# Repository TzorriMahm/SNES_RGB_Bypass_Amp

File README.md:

# SNES RGB Bypass Amp
**A modding board to bypass the SNES' video encoder by using TI's THS7374 video amplifier, to achieve optimised RGB video.**<br>

This modification works with all 1-Chip models (PAL/NTSC).

<br><br>
**⁓ Designed with ♥ in Germany ⁓**<br><br>

# Where to get the PCB?
You can order the PCB directly from [OSHPark](https://oshpark.com/shared_projects/o16zk0W4).
Of course, feel free to use the gerber files with any manufacturer of your choice.<br>
Use 0.8mm board thickness to ensure an easy and clean installation.

# Before you start
Make sure that your console is a 1-Chip model. If your console is a SNES2/Mini/Jr., this is the case by default.<br>
Otherwise, this can easily done by looking for an indicator at the main board:

# Install instructions
## PAL consoles (SNSP-001)
### Preparing the SNES main board
**1-CHIP-01/02 models**
- disconnect +12V from MultiOut Pin 3: **remove R28**
- disconnect stock RGB: **remove R15, R16, R17**
- remove decoupling caps from MultiOut (optional**¹**): **remove C44, C45, C46, C47**

### Installing the modding board
- isolate the bottom side of the modding board to avoid any shorts
- solder the modding board onto the pins of the MultiOut
- solder a wire from the via next to R6 (SNES main board) to pad 'R' (modding board)
- solder a wire from the via next to R7 (SNES main board) to pad 'G' (modding board)
- solder a wire from the via next to R8 (SNES main board) to pad 'B' (modding board)  
- solder a wire from the via that is nearest the bottom left corner of designator C6 (SNES main board) to pad 'CS' (modding board)  

### Install diagram (PAL 1-CHIP)

## NTSC consoles (SNS-001/SHVC-001)
### Preparing the SNES main board
**1-CHIP-01/02 models**<br>
These models already have C-Sync connected to pin 3 of the MultiOut.<br>
You can either use this (not recommended) or:
- disconnect C-Sync from MultiOut Pin 3: **remove R12** (optionally **remove R9, R10, R11, Q1** as well)
- disconnect stock RGB: **remove R15, R16, R17**
- remove decoupling caps from MultiOut (optional**¹**): **remove C44, C45, C46, C47**

**1-CHIP-03 model**<br>
This model hasn't C-Sync connected at all, so you'll have nothing to do here.
- disconnect stock RGB:	**remove R15, R16, R17**
- remove decoupling caps from MultiOut (optional**¹**'**²**):	**remove C44, C45, C47**

### Installing the modding board
- isolate the bottom side of the modding board to avoid any shorts
- solder the modding board onto the pins of the MultiOut
- solder a wire from the via next to R6 (SNES main board) to pad 'R' (modding board)
- solder a wire from the via next to R7 (SNES main board) to pad 'G' (modding board)
- solder a wire from the via next to R8 (SNES main board) to pad 'B' (modding board) 
- solder a wire from the via under the left pad of R9 (SNES main board) to pad 'CS' (modding board)

### Install diagram (NTSC 1-CHIP)

## NTSC model 2 / SNES2/Mini/Jr. (SNS-101/SHVC-101)
### Preparing the SNES main board
**SNN-CPU-01 model**<br>
Since this model doesn't have stock RGB, here is no preparation needed.

### Installing the modding board
- isolate the bottom side of the modding board to avoid any shorts
- solder the modding board onto the pins of the MultiOut
- solder wires from the vias (shown in the install diagram below) to the appropriate pads on the modding board

### Install diagram (SNES2/Mini/Jr.)

### Notes
**¹** if you remove the decoupling caps at the MultiOut, make sure to occupy C22, C32, C42 & C51 on the modding board! Never use both at the same time!<br>
**²** if you leave the decoupling caps at the MultiOut, make sure to occupy **at least** C51 on the modding board! (1-CHIP-03 only!) 

# Troubleshooting
Double-check continuity between connections:
- 'R' (modding board) ⇄ S-CPUN pin 156 / S-RGB pin 5 (SNES main board)
- 'G' (modding board) ⇄ S-CPUN pin 157 / S-RGB pin 3 (SNES main board)
- 'B' (modding board) ⇄ S-CPUN pin 158 / S-RGB pin 1 (SNES main board)
- 'CS' (modding board) ⇄ S-CPUN pin 151 / S-RGB pin 7 (SNES main board)

# Miscellaneous
#### Jumper 'J:LPF'
The THS7374 has a low pass filter on each of the four channels which can be turned on by shorting jumper 'J:LPF' on the modding board. This is mostly needed if you wire the console directly to a flat-screen TV. There's no need for the low pass filter on analogue devices.<br>
If you use an OSSC or a Framemeister, it's better to use their filter options.

#### Ghosting fix
In order to get rid of the ghosting issue (which 1-Chip models are known for), simply replace C11 (SNES main board) by a 470nF ceramic capacitor (0805 for normal/fat models, 0603 for SNES2/Mini/Jr.).

#### RGB cable
You will need a RGB cable with 220µF electrolytic capacitors on each of the 'R', 'G' & 'B' lines. The positive end is facing towards the console.<br>
This modding board is designed to output TTL level C-Sync directly at the MultiOut of the console.<br>
With that in mind, make sure you're using a suitable cable with a 470Ω resistor on the sync line to use it with most consumer products (like TV's, OSSC, Framemeister)!

# Disclaimer
I am not responsible for any damage to you, your devices or anything else!<br>
If you do the modification, you do it at your own risk and responsibility!

# Acknowledgement
Most of the credits should go to [borti4938](https://github.com/borti4938). He has made the actual (slightly different) circuit and inspired me to design this board. Thanks man! Thanks to Voultar for research and findig the ghosting fix! Thanks Bob, for your awesome and informative website [RetroRGB](http://retrorgb.com)!<br>
And of course, thanks to the whole retro gaming community for keeping the spirit alive!

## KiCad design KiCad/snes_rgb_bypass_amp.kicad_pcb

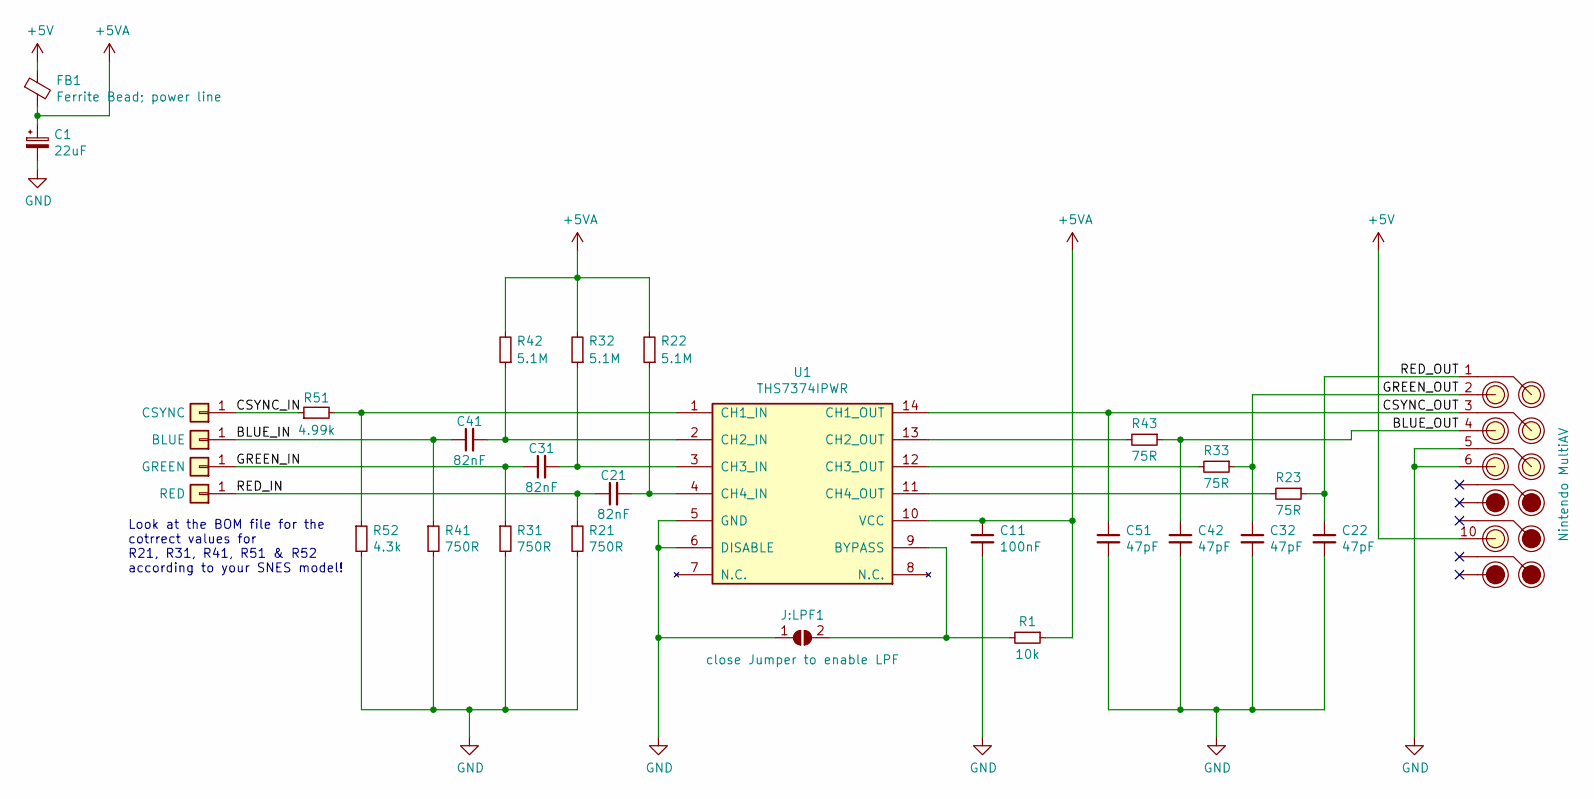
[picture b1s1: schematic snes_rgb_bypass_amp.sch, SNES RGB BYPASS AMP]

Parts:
C1: 22uF; C_SMD0805
C11: 100nF; C_SMD0603
C21, C31, C41: 82nF; C_SMD0603
C22, C32, C42, C51: 47pF; C_SMD0603
FB1: Ferrite Bead; power line; FB_SMD0603
INPUT_1: RED; SolderPad_customizable
INPUT_2: GREEN; SolderPad_customizable
INPUT_3: BLUE; SolderPad_customizable
INPUT_4: CSYNC; SolderPad_customizable
J:LPF1: close Jumper to enable LPF; SolderJumper_2x0.5x0.75mm
MultiAV1: Nintendo MultiAV; NintendoMultiAV_FB-gap
R1: 10k; R_SMD0603
R21, R31, R41: 750R; R_SMD0603
R22, R32, R42: 5.1M; R_SMD0603
R23, R33, R43: 75R; R_SMD0603
R51: 4.99k; R_SMD0603
R52: 4.3k; R_SMD0603
U1: THS7374IPWR; TSSOP-14

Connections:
+5V: FB1.1, MultiAV1.10
+5VA: C1.1, C11.1, FB1.2, R1.1, R22.2, R32.2, R42.2, U1.10 (VCC)
/BLUE_IN: C41.1, INPUT_3.1, R41.1
/BLUE_OUT: C42.1, MultiAV1.4, R43.1
/CSYNC_IN: INPUT_4.1, R51.1
/CSYNC_OUT: C51.1, MultiAV1.3, U1.14 (CH1_OUT)
/GREEN_IN: C31.1, INPUT_2.1, R31.1
/GREEN_OUT: C32.1, MultiAV1.2, R33.1
/RED_IN: C21.1, INPUT_1.1, R21.1
/RED_OUT: C22.1, MultiAV1.1, R23.1
GND: C1.2, C11.2, C22.2, C32.2, C42.2, C51.2, J:LPF1.1 (A), MultiAV1.5, MultiAV1.6, R21.2, R31.2, R41.2, R52.2, U1.5 (GND), U1.6 (DISABLE)
unnamed: C21.2, R22.1, U1.4 (CH4_IN)
unnamed: C31.2, R32.1, U1.3 (CH3_IN)
unnamed: C41.2, R42.1, U1.2 (CH2_IN)
unnamed: J:LPF1.2 (B), R1.2, U1.9 (BYPASS)
unnamed: R23.2, U1.11 (CH4_OUT)
unnamed: R33.2, U1.12 (CH3_OUT)
unnamed: R43.2, U1.13 (CH2_OUT)
unnamed: R51.2, R52.1, U1.1 (CH1_IN)

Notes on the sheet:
Look at the BOM file for the cotrrect values for R21, R31, R41, R51 & R52 according to your SNES model!

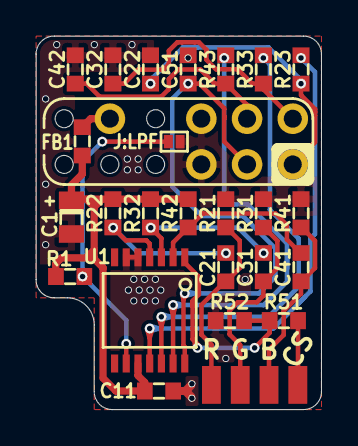
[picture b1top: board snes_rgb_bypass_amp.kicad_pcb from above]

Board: 2 copper layers, 15.9 x 20.8 mm, 30 parts (1 on the bottom side), 19 nets.

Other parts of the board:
***: TM_logo-silk

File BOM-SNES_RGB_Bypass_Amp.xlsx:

SNES RGB Bypass Amp - Bill of Materials
for normal/fat models
Designator | Mfr. No | Quantity | Description | Package | Value | Mouser
U1 | THS7374IPWR | 1 | 4-Ch. SD Video Amp | TSSOP-14 |  | https://www.mouser.de/ProductDetail/Texas-Instruments/THS737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
C1 | 08053D226MAT2A | 1 | Ceramic capacitor; X5R; 25V | SMD0805 | 22µF / 20% | https://www.mouser.de/ProductDetail/AVX/08053D226MAT2A?qs=bx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
C11 | 06035C104KAT2A | 1 | Ceramic capacitor; X7R; 50V | SMD0603 | 100nF / 10% | https://www.mouser.de/ProductDetail/AVX/06035C104KAT2A?qs=wO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
C21, C31, C31 | 0603YC823KAT2A | 3 | Ceramic capacitor; X7R; 16V | SMD0603 | 82nF / 10% | https://www.mouser.de/ProductDetail/AVX/0603YC823KAT2A?qs=Gc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
C22, C32, C42, C51 | 0603YC470KAT2A | 4 | Ceramic capacitor; X7R, 16V | SMD0603 | 47pF / 10% | https://www.mouser.de/ProductDetail/AVX/0603YC470KAT2A?qs=EU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
FB1 | MPZ1608S221ATA00 | 1 | Ferrite bead; power line | SMD0603 |  | https://www.mouser.de/ProductDetail/TDK/MPZ1608S221ATA00?qs=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
R1 | RC0603FR-0710KL | 1 | Resistor; 1/10W | SMD0603 | 10kΩ / 1% | https://www.mouser.de/ProductDetail/Yageo/RC0603FR-0710KL?qs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
R21, R31, R41 | RC0603FR-07750RL | 3 | Resistor; 1/10W | SMD0603 | 750Ω / 1% | https://www.mouser.de/ProductDetail/Yageo/RC0603FR-07750RL?q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
R22, R32, R42 | RC0603FR-075M1L | 3 | Resistor; 1/10W | SMD0603 | 5.1MΩ / 1% | https://www.mouser.de/ProductDetail/Yageo/RC0603FR-075M1L?qs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
R23, R33, R43 | RC0603FR-0775RL | 3 | Resistor; 1/10W | SMD0603 | 75Ω / 1% | https://www.mouser.de/ProductDetail/Yageo/RC0603FR-0775RL?qs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
R51 | RC0603FR-074K99L | 1 | Resistor; 1/10W | SMD0603 | 4.99kΩ / 1% | https://www.mouser.de/ProductDetail/Yageo/RC0603FR-074K99L?q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
R52 | RC0603FR-074K3L | 1 | Resistor; 1/10W | SMD0603 | 4.3kΩ / 1% | https://www.mouser.de/ProductDetail/Yageo/RC0603FR-074K3L?qs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
Mouser Basket: | https://www.mouser.de/ProjectManager/ProjectDetail.aspx?Acce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

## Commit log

2020-12-17 Add KiCad files for v3.2
    - project file
    - schematics
    - design file
    - libraries
2020-12-17 Update README.md
    - changes the link to OSHPark
2020-12-17 Replace gerber files to match v3.2
2020-12-17 Update README.md
    - changes the link to OSHPark (again)
2020-12-17 minor fix of bottom silk screen
